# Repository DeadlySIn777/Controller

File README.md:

# Visual CNC controller — engineering workspace

Documentation reconciled **18 October 2026** against recorded decisions and evidence. The controller has working disconnected software, LinuxCNC/RTL integration and substantial native electrical/PCB work. Routing, complete electrical qualification, FPGA physical implementation and physical machine qualification remain unfinished. **There is no manufacturing release.**

## Start here

| Document | Purpose |
| --- | --- |
| [Complete documentation index](docs/README.md) | All topic guides, component documentation and historical evidence |
| [Project briefing](PROJECT_BRIEFING.md) | Product, architecture, implemented work and remaining work |
| [Project memory](PROJECT_MEMORY.md) | User decisions and constraints to preserve |
| [Engineering status](reports/ENGINEERING_STATUS.md) | Latest recorded results, exact sources and limitations |
| [Current acceptance gates](docs/CURRENT_ACCEPTANCE_GATES.md) | Requirements still needed for release |
| [Build plan](docs/BUILD_PLAN.md) and [platform roadmap](docs/PLATFORM_ROADMAP.md) | Execution order and proposed capabilities |

## Current product contract

[IS-2](docs/MOTHERBOARD_IS2.md) requires **one active custom motherboard with a soldered FPGA and all twelve motor interfaces fitted**, individual enable/alarm on all twelve, at least eight usable motors, four base ABZ encoders, 24 general DI and 16 smart general DO, plus the specified fast inputs, process/analog interfaces, communications, protection and watchdog/permission circuitry. Purchased compute, ESP and storage/settings modules remain replaceable. The older passive base, removable custom motion/I/O cards and motors-9–12 expansion card are superseded.

Local LinuxCNC owns motion planning; the FPGA supplies deterministic timing/capture and the ESP has a bounded diagnostic/service role. Accessory automation is a separately qualified extension. The touchscreen, CLI and optional AI proposals share validation and reversible configuration transactions. Normal operation and recovery remain available offline without AI credits. See [setup](docs/SETUP_WORKBENCH.md), [configuration](docs/CONFIGURATION_AND_CLI.md), [diagnostics](docs/DIAGNOSTICS_AND_PACKAGES.md) and [OS experience](docs/CONTROLLER_OS.md).

Screen options cover the **7-, 10-, 12-, 14-, 18- and 21-inch classes and further qualified sizes**. Screen size and software licensing do not remove fitted motor channels or required I/O. Every package must include and cost its stated display, compute, supplies, enclosure, harnesses and setup scope. See [display tiers](docs/DISPLAY_TIERS.md) and [commercial policy](docs/COMMERCIAL_MODEL_AND_LICENSING.md).

Power-off service exchanges an approved commodity module or the whole motherboard using keyed pluggable terminal/harness groups. Preserve protected machine settings, mirror/export recovery, offline entitlement and deliberate inhibited restart. Whole-board service has its own verification and cost requirements; no five-minute replacement guarantee is established. See [repair and machine memory](docs/MODULAR_REPAIR_AND_MEMORY.md).

## Evidence to read in context

| Scope | Recorded result | Boundary |
| --- | --- | --- |
| Adopted Source26/ROOT104, published CAD30 | 3,508 required joins remain; native ordinary DRC 0 errors/0 warnings; Source26 ERC 0 errors/70 warnings | Dated adopted source, distinct from later isolated finishing work |
| [17 October finishing continuation](reports/board-finish-20261017/README.md) | Recovered R299 full native result: 1,172 required joins / 1,183 API items, 0 ordinary errors/333 warnings/0 parity issues | Unfinished continuation; no adoption or manufacturing promotion |
| Isolated corrected baseline in that continuation | Same 1,172 joins; cached-fill DRC 0 ordinary errors/332 warnings/0 parity issues | Duplicate-via/BOM correction; no fresh refill in that check |
| Composed routing stages 1–4 | Native input/source/geometry checks recorded; full refill/AFTER qualification remains open in the cited report | Stale cached fills cannot establish new connectivity or ratings |
| Canonical disconnected SIM2 correction | Actual full-core mapping: 15,805 LUT4 + 2,107 ADD = 17,912; 63 RAM5K; fresh eight-/twelve-joint LinuxCNC/C/SPI/RTL/virtual-feedback checks | Functional mapping and simulation; physical wrapper, vendor place/route and timing remain open |
| Historical CNC1 baseline | [Six-joint/two-encoder integration](reports/CNC1_INTEGRATION.md), [synthesis](reports/FPGA_SYNTHESIS.md) and [recovery](reports/PERSISTENT_RUNTIME.md) | Preserve the original tested source, date, limits and profile |

Use the source-bound [engineering status](reports/ENGINEERING_STATUS.md) and continuation receipts before quoting a count. Source inspection, host tests, target compilation, HDL simulation, FPGA mapping, circuit ERC, board DRC and physical measurements establish different things. No physical commissioning or complete machine rating follows from the table.

The immutable [Source26 cost audit v11](reports/motherboard-cost-20260930/source-r26-2688-complete-cost-v11/README.md) is a dated partial basket: 105 exact MPNs priced, 185 MPNs/720 fitted pieces unpriced. Known-priced consumed parts at 1/10/100 controllers are US$1,091.51/$877.37/$796.51 per board. Modules, displays, fabrication, assembly, programming/test and packaging remain additional unknowns. US$400 is a preliminary assembly reference; a complete product cost or PCBWay quote is not established.

## Use the disconnected workbench

From this directory, with the required Python dependencies available:

```powershell
python -B -m controller_config setup --directory .controller-setup-demo serve --port 8766
```

Open `http://127.0.0.1:8766/`. This starts the local simulation setup UI and shared service. It does not commission or authorize a physical machine. The [workbench guide](docs/SETUP_WORKBENCH.md) describes intake, readiness, reviewed saves, backup recovery and optional AI budgets. Use a separate demonstration directory to preserve existing machine configurations.

To inspect the engineering bench before choosing checks:

```powershell
python -X utf8 tools/validate_controller.py --inventory
```

The documented full disconnected bench is `./validate_controller.ps1 --full` or `python -X utf8 tools/validate_controller.py --full`. It creates a new evidence directory. Missing tools and unfinished stages remain explicitly blocked; physical tests remain unrun. See [Rev A qualification](docs/REV_A_QUALIFICATION.md) and the [PCBWay submission checklist](manufacturing/PCBWAY_SUBMISSION_CHECKLIST.md).

The [200-feature catalogue](docs/FEATURE_CATALOG.md) preserves proposals and stable IDs. Dated research, component READMEs and report snapshots keep their original evidence scope; use the [documentation index](docs/README.md) to find current guidance before interpreting them as product capabilities.

## Published native board snapshot

The existing [board-review package](BOARD_REVIEW.md), its native baseline/staged files and original provenance remain available alongside the complete engineering source. See [GitHub publication scope](GITHUB_PUBLICATION.md) for the source/evidence inventory.

The [corrected global reroute start](board/global-reroute-start/board.kicad_pro), [clean DSN](routing/TMR-clean-plane-free-F-In3-B-domain600-r6.dsn) and [converter setup correction](review/TMR-setup-correction.md) are also available. They restore five malformed keepouts and remove 359 conflicting copper items for rerouting; native AFTER connectivity and manufacturing qualification remain open.

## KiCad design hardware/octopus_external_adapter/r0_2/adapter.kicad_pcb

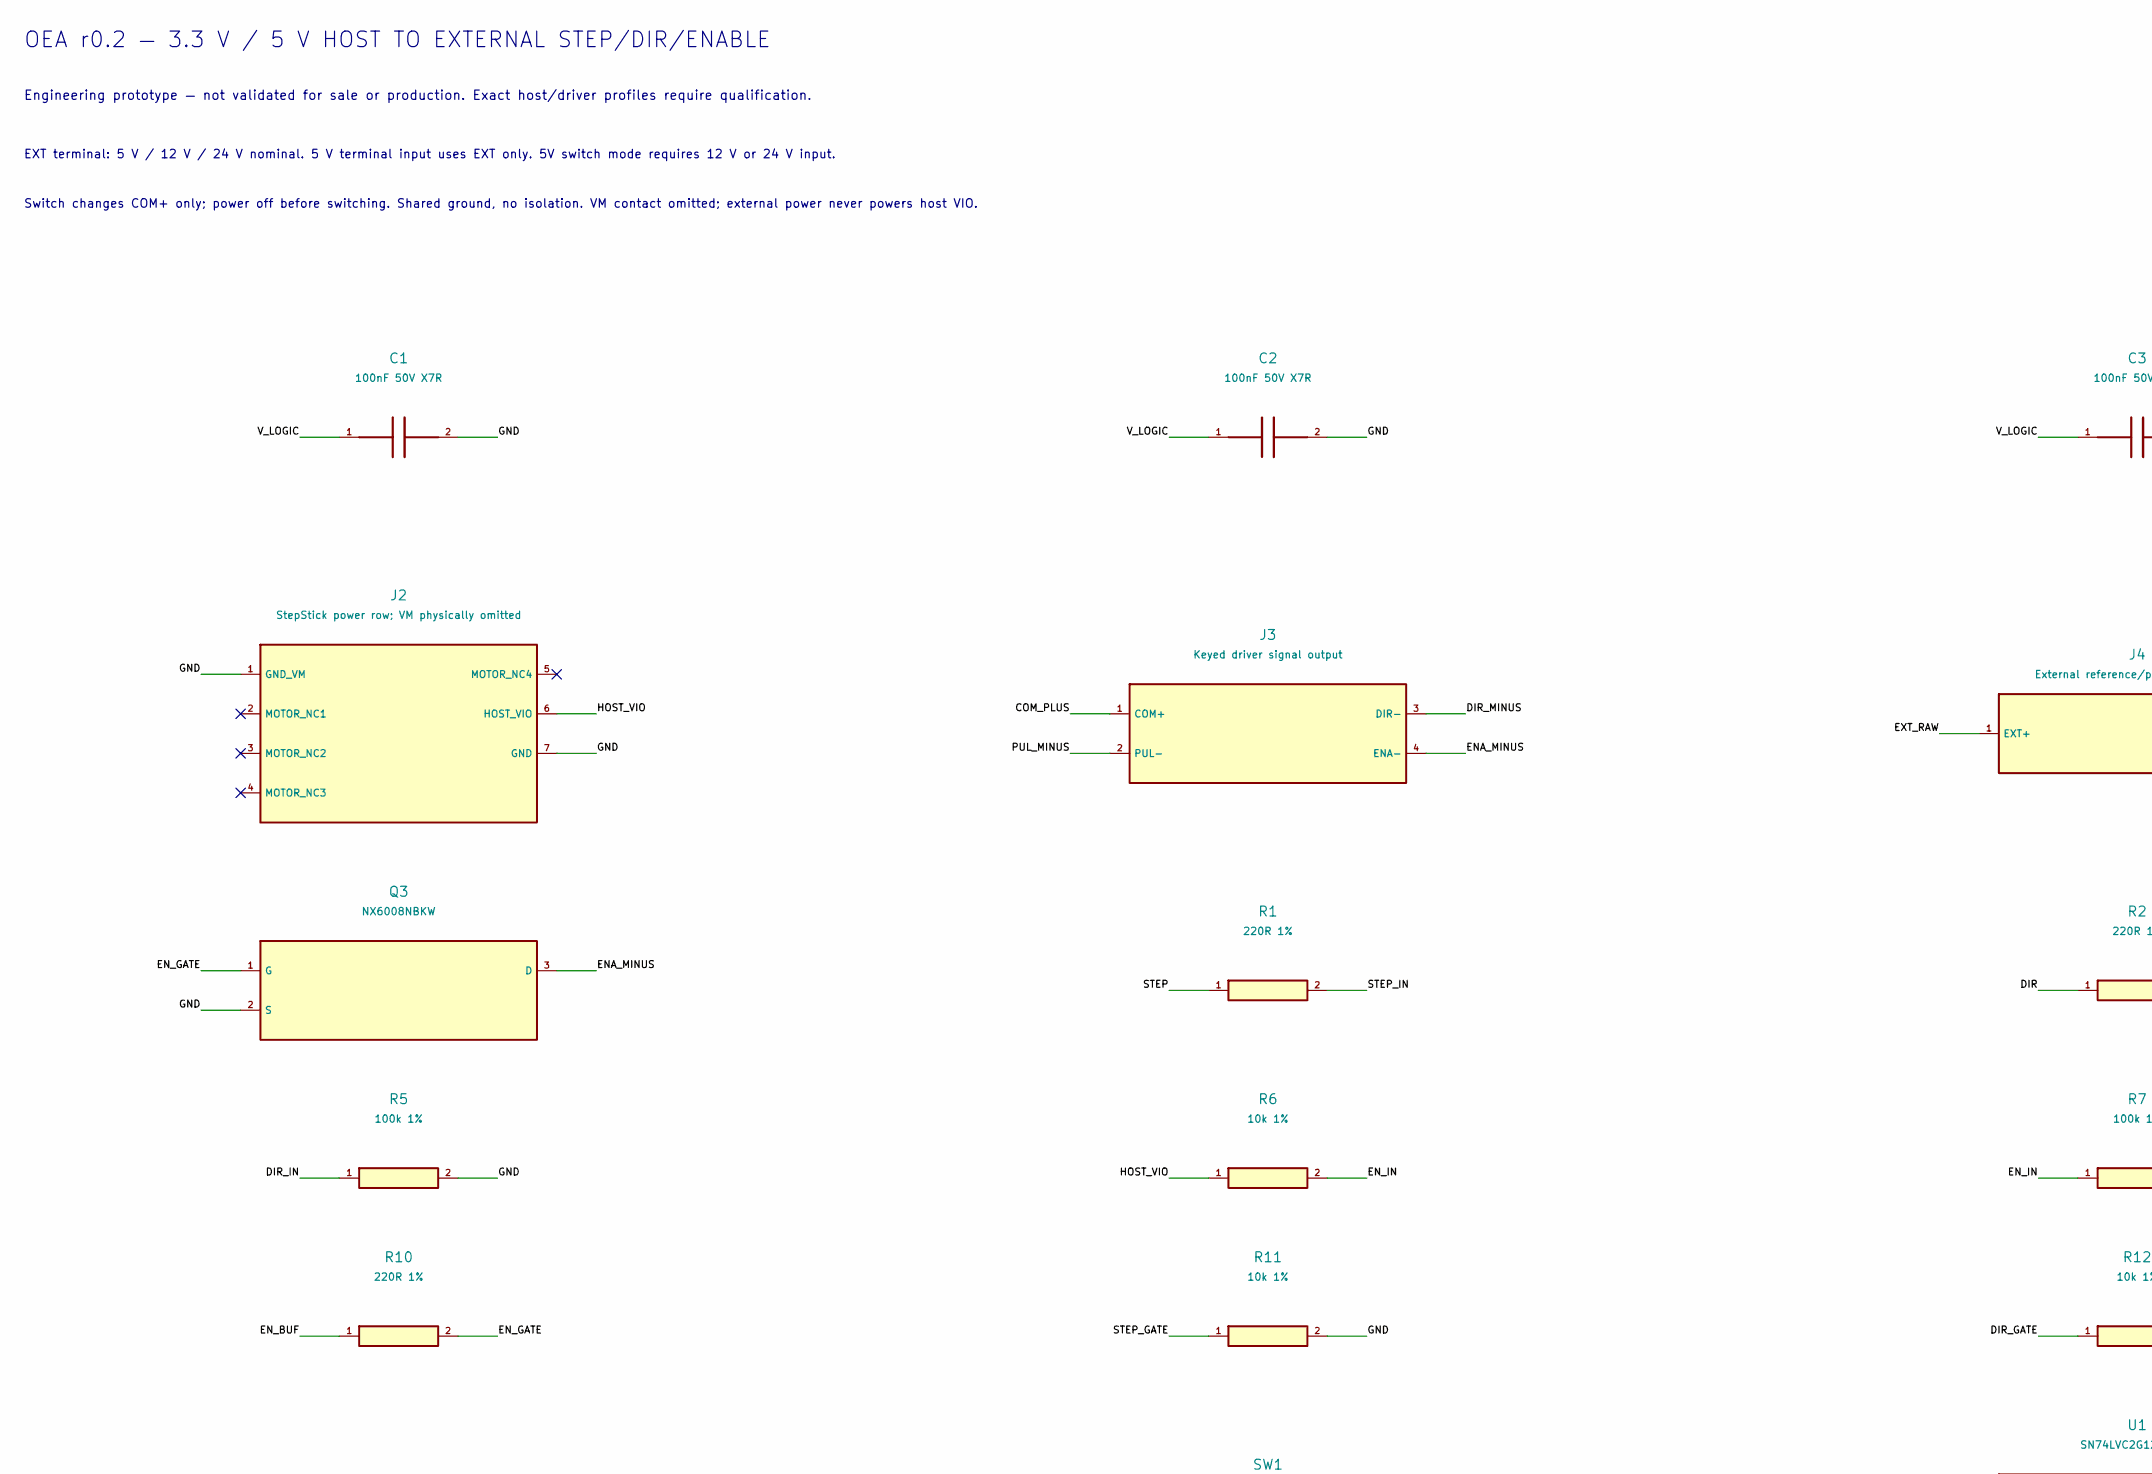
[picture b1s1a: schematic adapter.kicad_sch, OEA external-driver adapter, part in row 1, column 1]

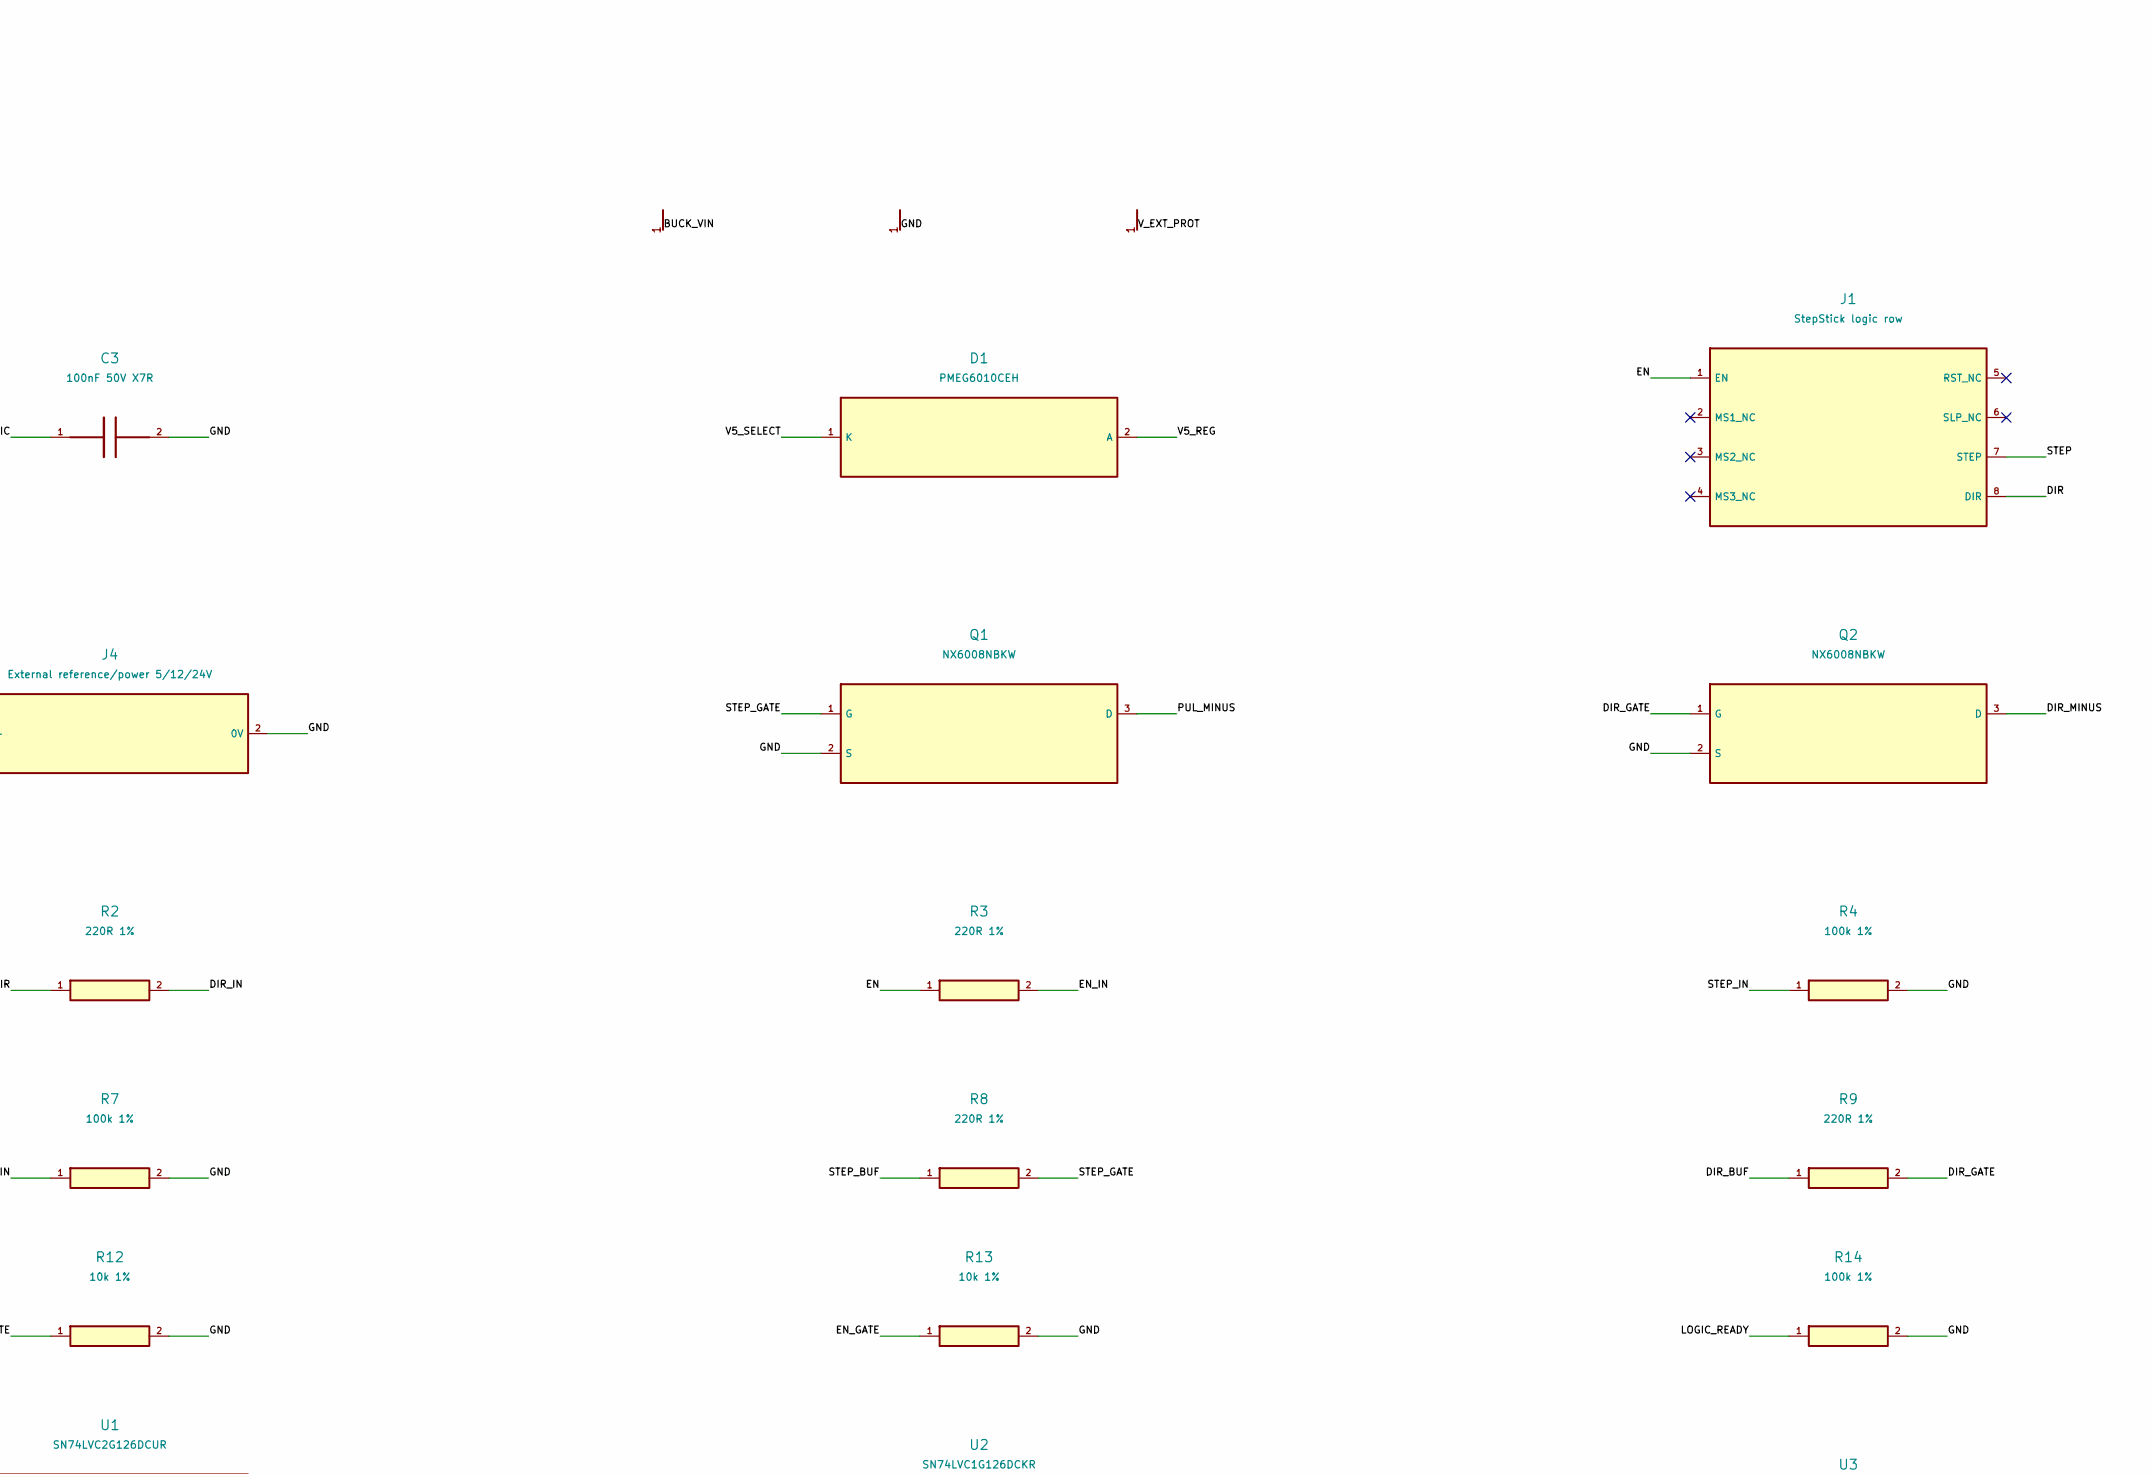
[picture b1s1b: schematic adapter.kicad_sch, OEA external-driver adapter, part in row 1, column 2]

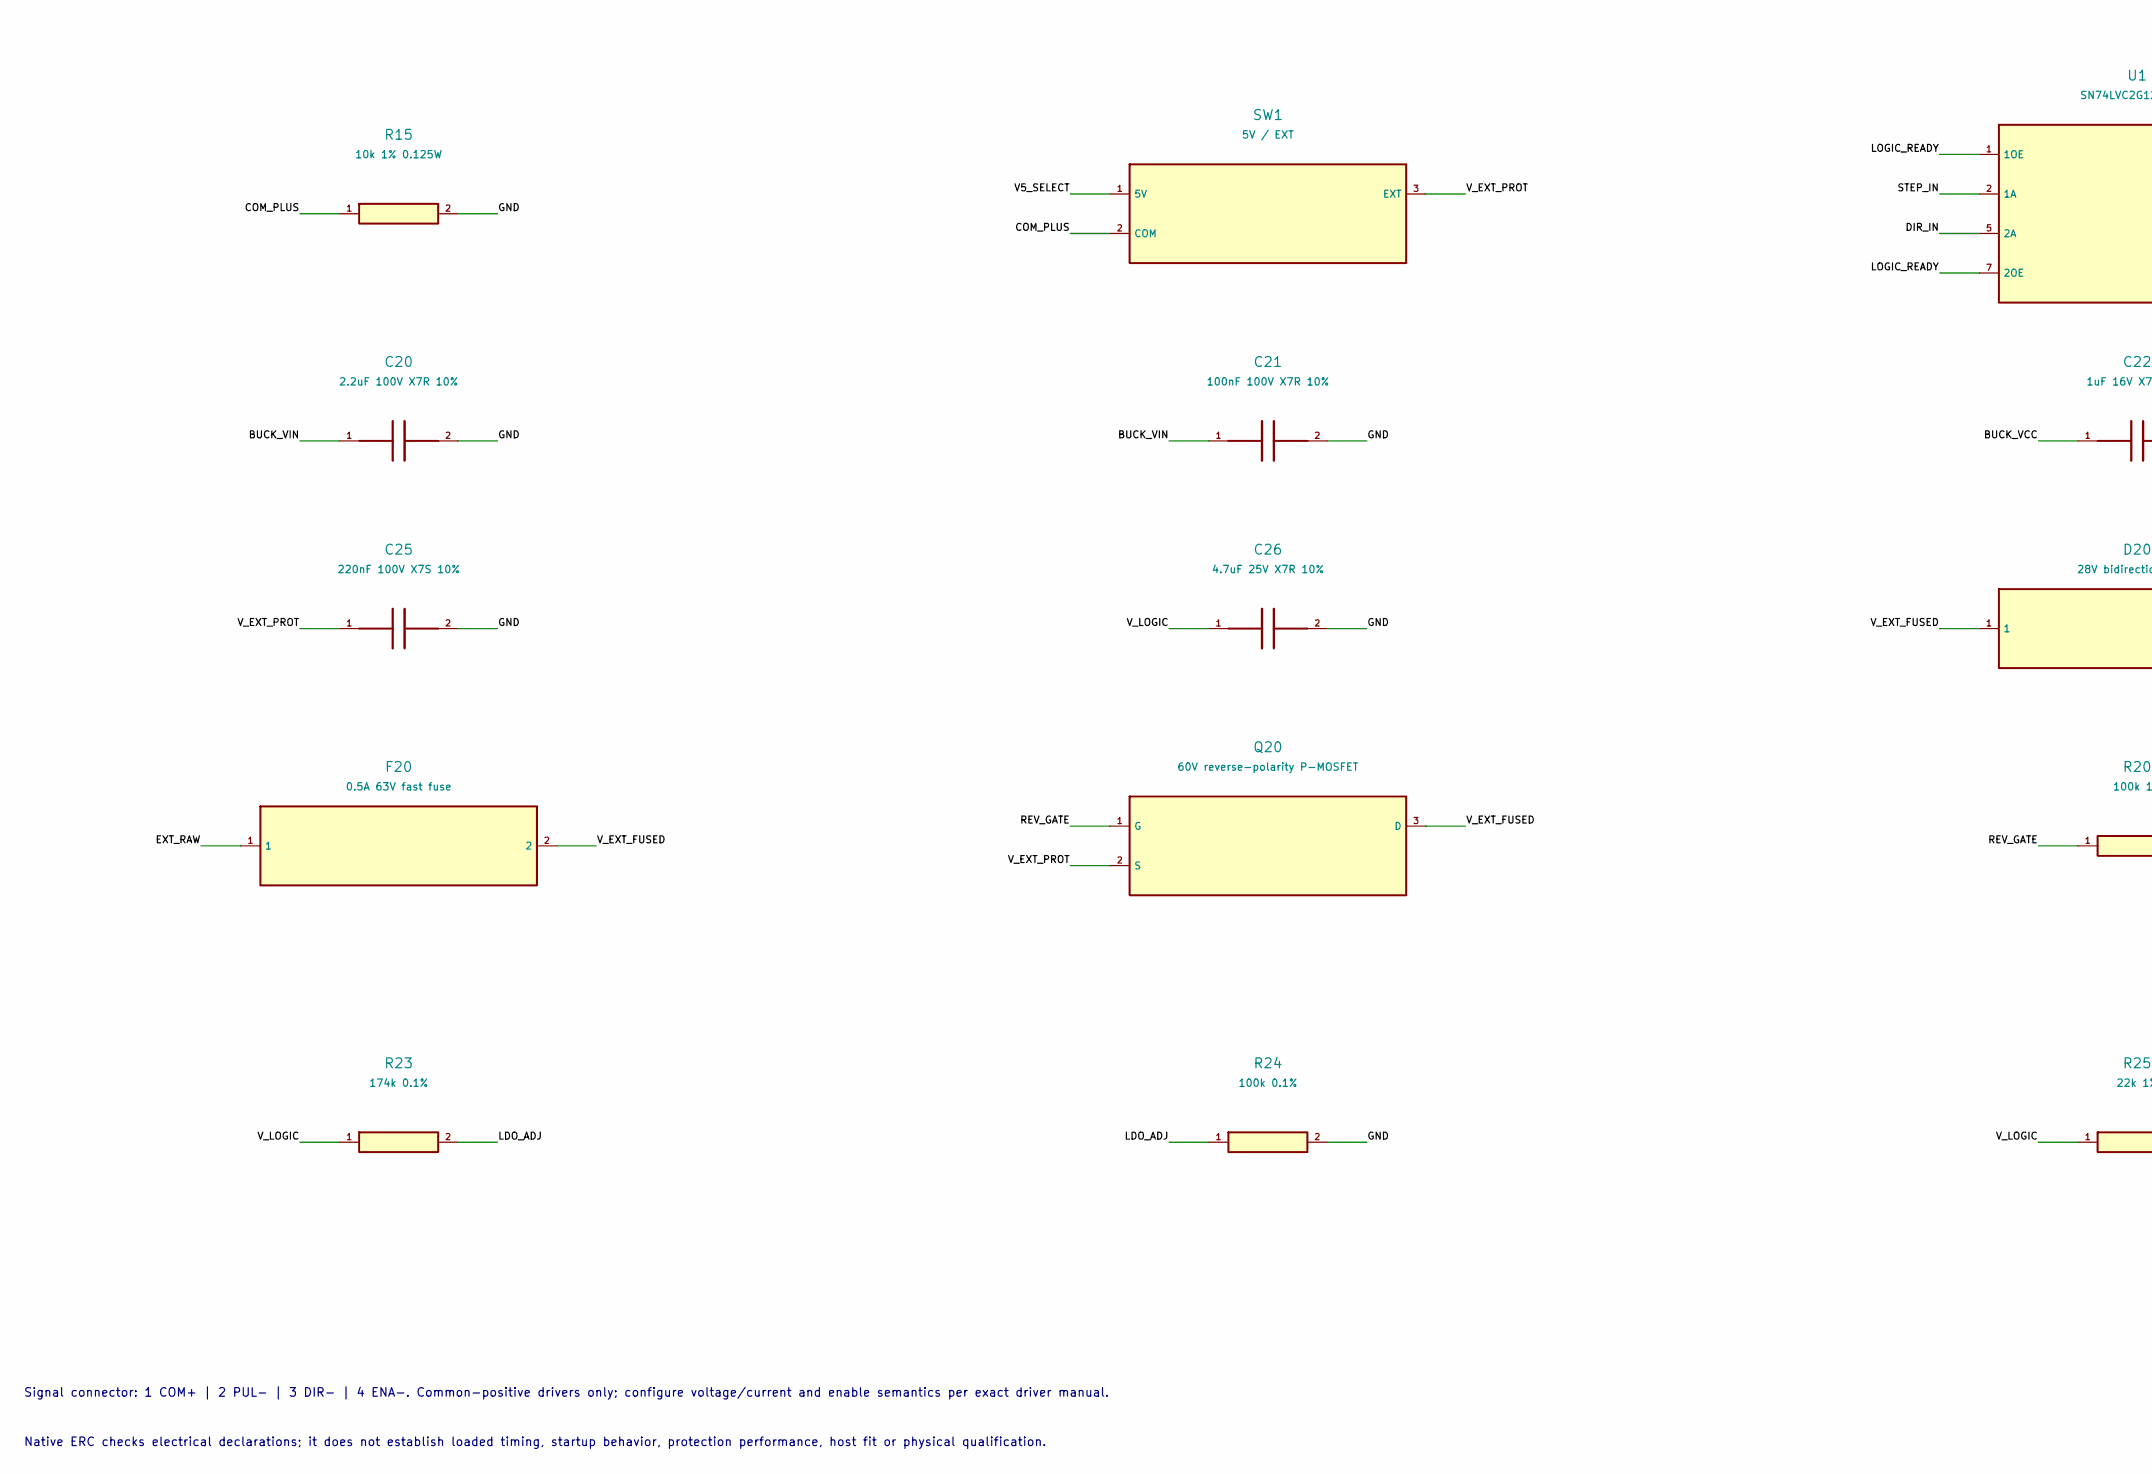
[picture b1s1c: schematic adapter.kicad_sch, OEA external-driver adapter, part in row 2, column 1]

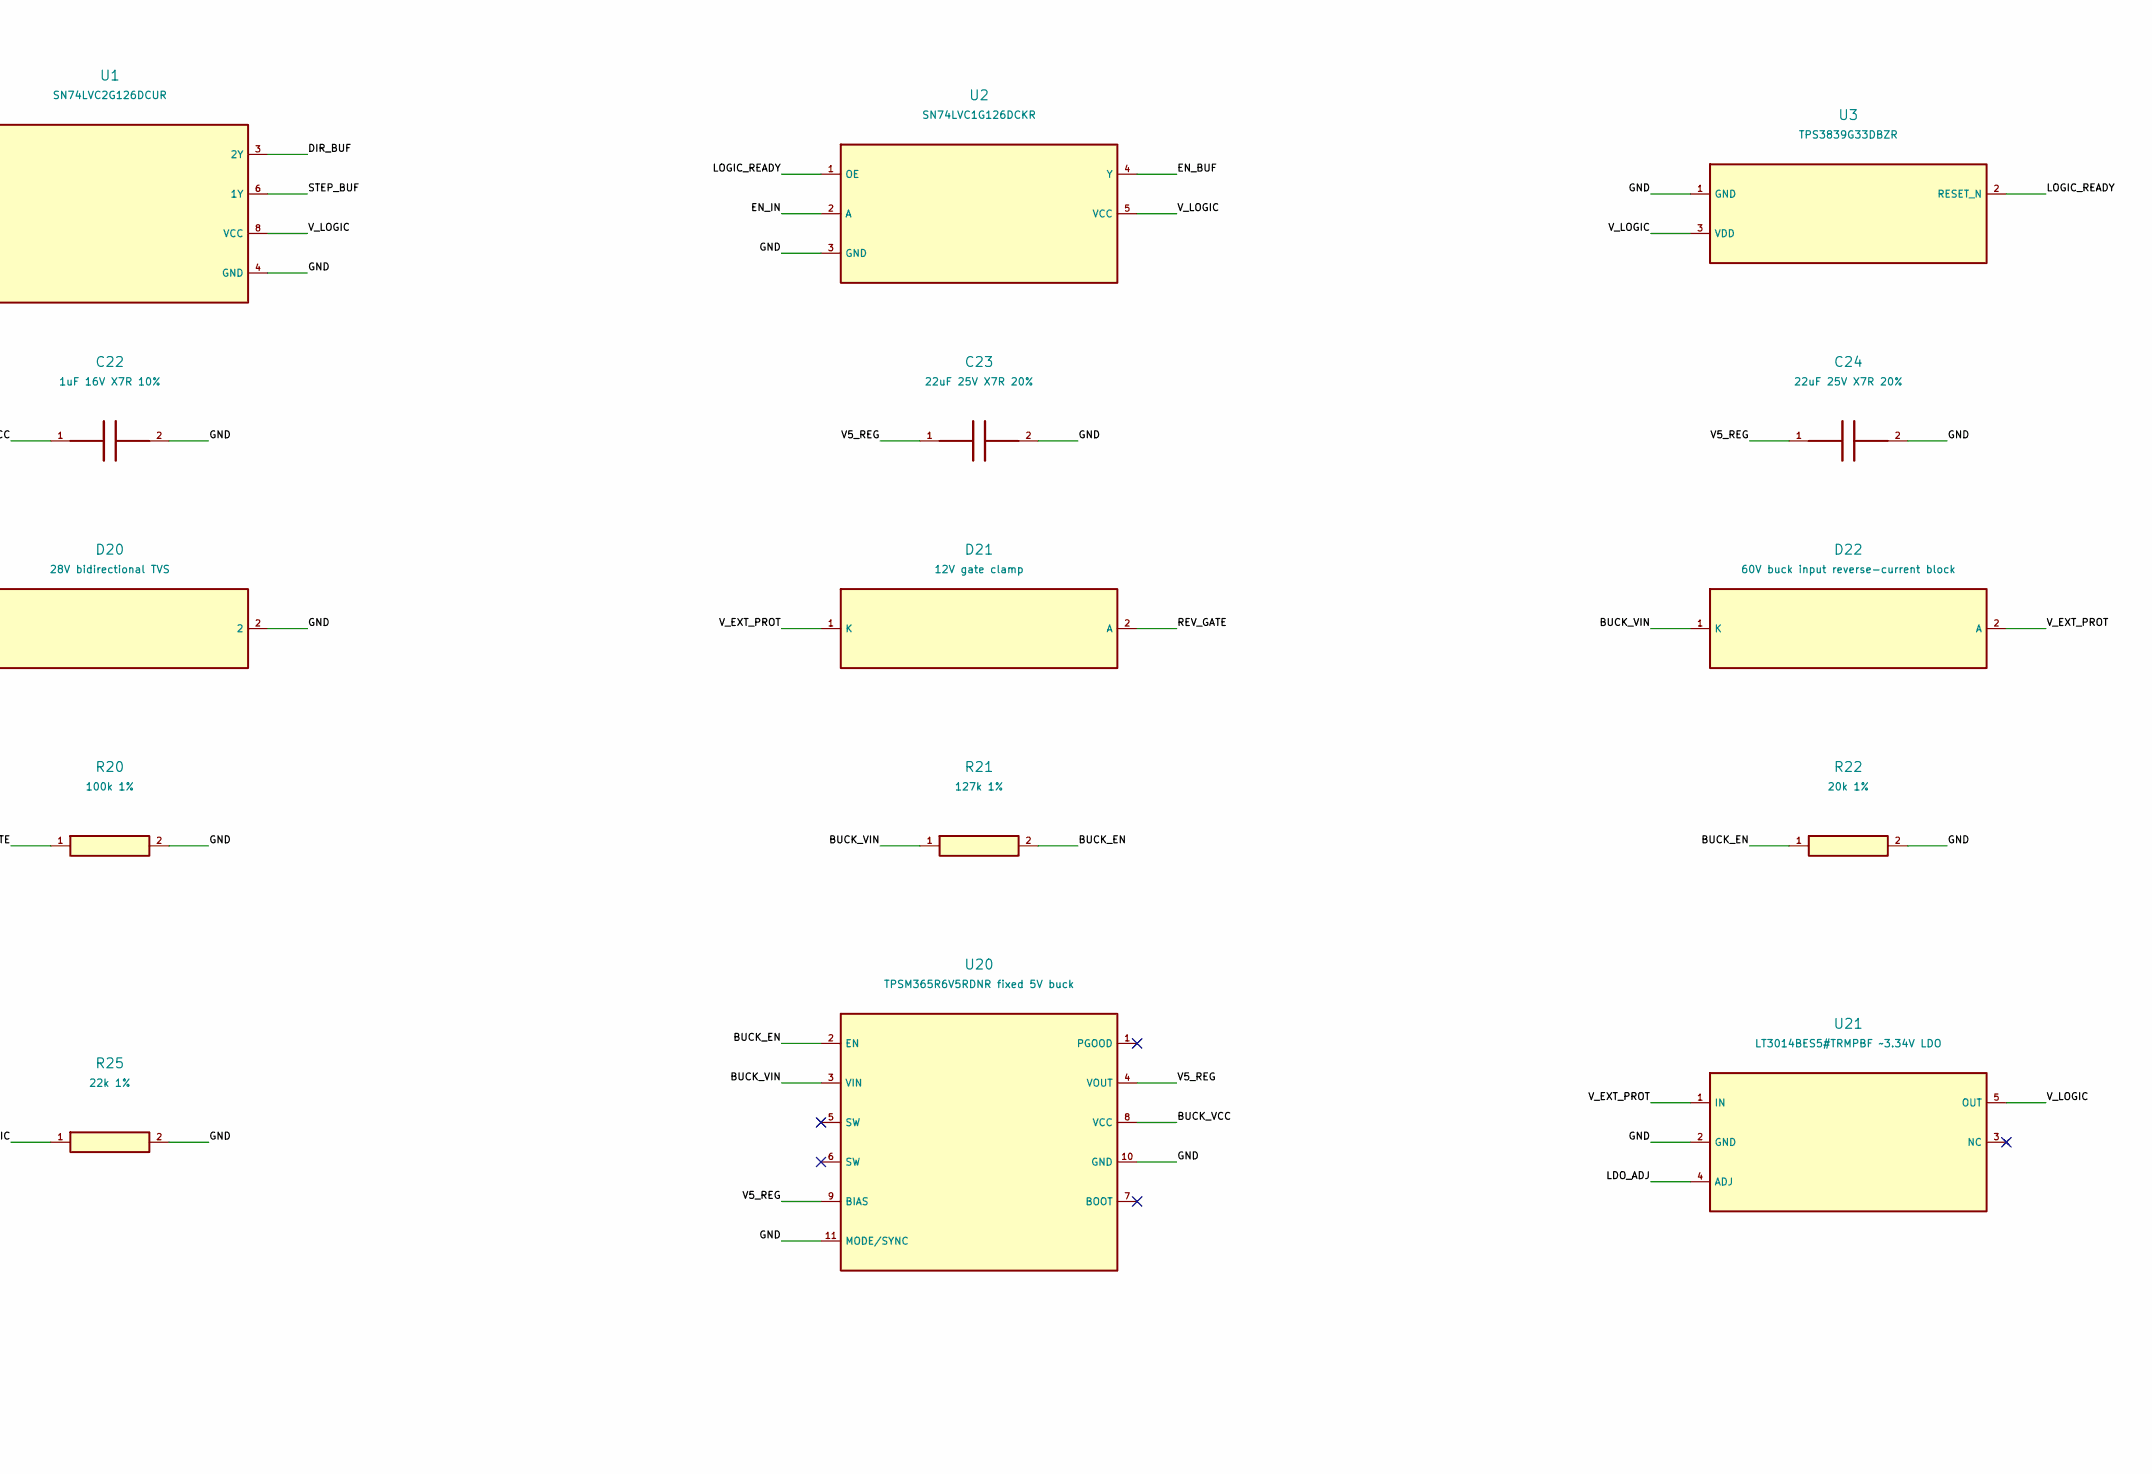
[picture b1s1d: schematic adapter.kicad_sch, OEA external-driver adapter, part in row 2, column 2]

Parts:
C1, C2, C3: 100nF 50V X7R; C_0603_1608Metric; MPN CL10B104KB8NNNC
C20: 2.2uF 100V X7R 10%; C_1210_3225Metric; MPN C3225X7R2A225K230AB
C21: 100nF 100V X7R 10%; C_0603_1608Metric; MPN GRM188R72A104KA35J
C22: 1uF 16V X7R 10%; C_0603_1608Metric; MPN C1608X7R1C105K080AC
C23, C24: 22uF 25V X7R 20%; C_1210_3225Metric; MPN C3225X7R1E226M250AB
C25: 220nF 100V X7S 10%; C_0805_2012Metric; MPN C2012X7S2A224K085AE
C26: 4.7uF 25V X7R 10%; C_0805_2012Metric; MPN CL21B475KAFNNNE
D1: PMEG6010CEH; D_SOD-123F; MPN PMEG6010CEH,115
D20: 28V bidirectional TVS; D_SMA; MPN SMAJ28CA-13-F
D21: 12V gate clamp; D_SOD-123; MPN BZT52C12-7-F
D22: 60V buck input reverse-current block; D_SOD-123F; MPN PMEG6010CEH,115
F20: 0.5A 63V fast fuse; Bourns_SF-1206F_3.1x1.55mm; MPN SF-1206F050-2
J1: StepStick logic row; Wurth_61300811121_1x08_P2.54mm; MPN 61300811121
J2: StepStick power row; VM physically omitted; Wurth_61300711121_1x07_P2.54mm; MPN 61300711121
J3: Keyed driver signal output; JST_XH_B4B-XH-A_1x04_P2.50mm_Vertical; MPN B4B-XH-A(LF)(SN)
J4: External reference/power 5/12/24V; Phoenix_1725656_MPT_0p5_2_2p54_SilkClearance; MPN 1725656
Q1, Q2, Q3: NX6008NBKW; SOT-323_SC-70; MPN NX6008NBKW,115
Q20: 60V reverse-polarity P-MOSFET; SOT-23; MPN PMV100EPAR
R1, R2, R3, R8, R9, R10: 220R 1%; R_0603_1608Metric; MPN RC0603FR-07220RL
R4, R5, R7, R14, R20: 100k 1%; R_0603_1608Metric; MPN RC0603FR-07100KL
R6, R11, R12, R13: 10k 1%; R_0603_1608Metric; MPN RC0603FR-0710KL
R15: 10k 1% 0.125W; R_0805_2012Metric; MPN RC0805FR-0710KL
R21: 127k 1%; R_0603_1608Metric; MPN RC0603FR-07127KL
R22: 20k 1%; R_0603_1608Metric; MPN RC0603FR-0720KL
R23: 174k 0.1%; R_0603_1608Metric; MPN RT0603BRD07174KL
R24: 100k 0.1%; R_0603_1608Metric; MPN RT0603BRD07100KL
R25: 22k 1%; R_0603_1608Metric; MPN RC0603FR-0722KL
SW1: 5V / EXT; E-Switch_EG1218_P040040; MPN EG1218
U1: SN74LVC2G126DCUR; VSSOP-8_2.3x2mm_P0.5mm; MPN SN74LVC2G126DCUR
U2: SN74LVC1G126DCKR; SOT-353_SC-70-5; MPN SN74LVC1G126DCKR
U3: TPS3839G33DBZR; SOT-23; MPN TPS3839G33DBZR
U20: TPSM365R6V5RDNR fixed 5V buck; TI_RDN0011A_TPSM365R6; MPN TPSM365R6V5RDNR
U21: LT3014BES5#TRMPBF ~3.34V LDO; TSOT-23-5; MPN LT3014BES5#TRMPBF

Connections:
/BUCK_EN: R21.2, R22.1, U20.2 (EN)
/BUCK_VCC: C22.1, U20.8 (VCC)
/BUCK_VIN: C20.1, C21.1, D22.1 (K), R21.1, U20.3 (VIN)
/COM_PLUS: J3.1 (COM+), R15.1, SW1.2 (COM)
/DIR: J1.8 (DIR), R2.1
/DIR_BUF: R9.1, U1.3 (2Y)
/DIR_GATE: Q2.1 (G), R9.2, R12.1
/DIR_IN: R2.2, R5.1, U1.5 (2A)
/DIR_MINUS: J3.3 (DIR-), Q2.3 (D)
/EN: J1.1 (EN), R3.1
/ENA_MINUS: J3.4 (ENA-), Q3.3 (D)
/EN_BUF: R10.1, U2.4 (Y)
/EN_GATE: Q3.1 (G), R10.2, R13.1
/EN_IN: R3.2, R6.2, R7.1, U2.2 (A)
/EXT_RAW: F20.1, J4.1 (EXT+)
/GND: C1.2, C2.2, C3.2, C20.2, C21.2, C22.2, C23.2, C24.2, C25.2, C26.2, D20.2, J2.1 (GND_VM), J2.7 (GND), J4.2 (0V), Q1.2 (S), Q2.2 (S), Q3.2 (S), R4.2, R5.2, R7.2, R11.2, R12.2, R13.2, R14.2, R15.2, R20.2, R22.2, R24.2, R25.2, U1.4 (GND), U2.3 (GND), U3.1 (GND), U20.10 (GND), U20.11 (MODE/SYNC), U21.2 (GND)
/HOST_VIO: J2.6 (HOST_VIO), R6.1
/LDO_ADJ: R23.2, R24.1, U21.4 (ADJ)
/LOGIC_READY: R14.1, U1.1 (1OE), U1.7 (2OE), U2.1 (OE), U3.2 (RESET_N)
/PUL_MINUS: J3.2 (PUL-), Q1.3 (D)
/REV_GATE: D21.2 (A), Q20.1 (G), R20.1
/STEP: J1.7 (STEP), R1.1
/STEP_BUF: R8.1, U1.6 (1Y)
/STEP_GATE: Q1.1 (G), R8.2, R11.1
/STEP_IN: R1.2, R4.1, U1.2 (1A)
/V5_REG: C23.1, C24.1, D1.2 (A), U20.4 (VOUT), U20.9 (BIAS)
/V5_SELECT: D1.1 (K), SW1.1 (5V)
/V_EXT_FUSED: D20.1, F20.2, Q20.3 (D)
/V_EXT_PROT: C25.1, D21.1 (K), D22.2 (A), Q20.2 (S), SW1.3 (EXT), U21.1 (IN)
/V_LOGIC: C1.1, C2.1, C3.1, C26.1, R23.1, R25.1, U1.8 (VCC), U2.5 (VCC), U3.3 (VDD), U21.5 (OUT)

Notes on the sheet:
OEA r0.2 — 3.3 V / 5 V HOST TO EXTERNAL STEP/DIR/ENABLE
Engineering prototype — not validated for sale or production. Exact host/driver profiles require qualification.
EXT terminal: 5 V / 12 V / 24 V nominal. 5 V terminal input uses EXT only. 5V switch mode requires 12 V or 24 V input.
Switch changes COM+ only; power off before switching. Shared ground, no isolation. VM contact omitted; external power never powers host VIO.
Signal connector: 1 COM+ | 2 PUL− | 3 DIR− | 4 ENA−. Common-positive drivers only; configure voltage/current and enable semantics per exact driver manual.
Native ERC checks electrical declarations; it does not establish loaded timing, startup behavior, protection performance, host fit or physical qualification.

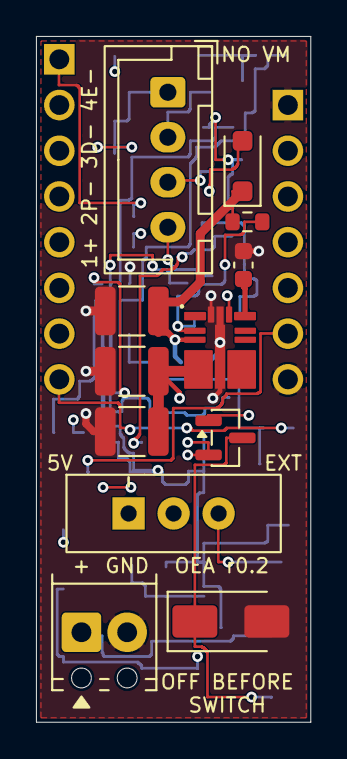
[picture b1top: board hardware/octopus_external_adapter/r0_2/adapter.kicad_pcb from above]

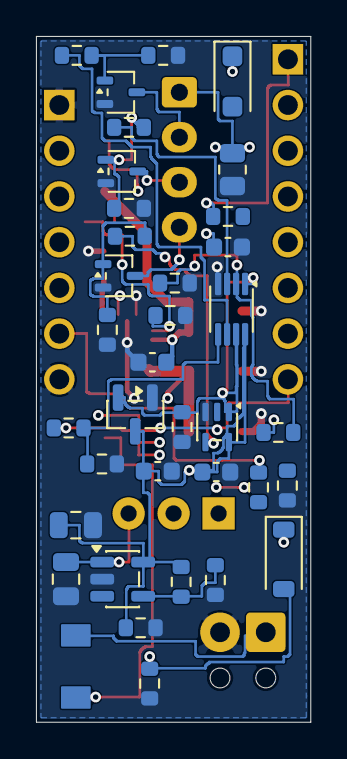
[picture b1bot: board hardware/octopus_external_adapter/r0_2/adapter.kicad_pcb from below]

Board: 4 copper layers, 15.2 x 38.1 mm, 50 parts (38 on the bottom side), 30 nets.

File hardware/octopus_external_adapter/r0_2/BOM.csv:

Item,Designators,Quantity per board,Quantity for 5 boards,Manufacturer,Manufacturer part number,Description / value,Footprint,Mounting,Assembly side by reference,Fit,Assembly notes
1,"C1, C2, C3",3,15,Samsung Electro-Mechanics,CL10B104KB8NNNC,100nF 50V X7R,Capacitor_SMD:C_0603_1608Metric,SMT,C1: Bottom; C2: Bottom; C3: Bottom,Yes,No substitutions without engineering approval.
2,C20,1,5,TDK,C3225X7R2A225K230AB,2.2uF 100V X7R 10%,Capacitor_SMD:C_1210_3225Metric,SMT,C20: Top,Yes,No substitutions without engineering approval.
3,C21,1,5,Murata,GRM188R72A104KA35J,100nF 100V X7R 10%,Capacitor_SMD:C_0603_1608Metric,SMT,C21: Bottom,Yes,No substitutions without engineering approval.
4,C22,1,5,TDK,C1608X7R1C105K080AC,1uF 16V X7R 10%,Capacitor_SMD:C_0603_1608Metric,SMT,C22: Top,Yes,No substitutions without engineering approval.
5,"C23, C24",2,10,TDK,C3225X7R1E226M250AB,22uF 25V X7R 20%,Capacitor_SMD:C_1210_3225Metric,SMT,C23: Top; C24: Top,Yes,No substitutions without engineering approval.
6,C25,1,5,TDK,C2012X7S2A224K085AE,220nF 100V X7S 10%,Capacitor_SMD:C_0805_2012Metric,SMT,C25: Bottom,Yes,No substitutions without engineering approval.
7,C26,1,5,Samsung Electro-Mechanics,CL21B475KAFNNNE,4.7uF 25V X7R 10%,Capacitor_SMD:C_0805_2012Metric,SMT,C26: Bottom,Yes,No substitutions without engineering approval.
8,"D1, D22",2,10,Nexperia,"PMEG6010CEH,115",PMEG6010CEH; 60V buck input reverse-current block,Diode_SMD:D_SOD-123F,SMT,D1: Bottom; D22: Top,Yes,No substitutions without engineering approval.
9,D20,1,5,Diodes Incorporated,SMAJ28CA-13-F,28V bidirectional TVS,Diode_SMD:D_SMA,SMT,D20: Top,Yes,No substitutions without engineering approval.
10,D21,1,5,Diodes Incorporated,BZT52C12-7-F,12V gate clamp,Diode_SMD:D_SOD-123,SMT,D21: Bottom,Yes,No substitutions without engineering approval.
11,F20,1,5,Bourns,SF-1206F050-2,0.5A 63V fast fuse,Adapter:Bourns_SF-1206F_3.1x1.55mm,SMT,F20: Bottom,Yes,No substitutions without engineering approval.
12,J1,1,5,Wurth Elektronik,61300811121,StepStick logic row,Adapter:Wurth_61300811121_1x08_P2.54mm,THT,J1: Bottom,Yes,No substitutions without engineering approval. Long male mating posts face down into host; do not trim mating posts.
13,J2,1,5,Wurth Elektronik,61300711121,StepStick power row; VM physically omitted,Adapter:Wurth_61300711121_1x07_P2.54mm,THT,J2: Bottom,Yes,No substitutions without engineering approval. Long male mating posts face down into host; do not trim mating posts.
14,J3,1,5,JST,B4B-XH-A(LF)(SN),Keyed driver signal output,Connector_JST:JST_XH_B4B-XH-A_1x04_P2.50mm_Vertical,THT,J3: Top,Yes,No substitutions without engineering approval. Controlled underside tail trimming per assembly drawing.
15,J4,1,5,Phoenix Contact,1725656,External reference/power 5/12/24V,"TerminalBlock_Phoenix:TerminalBlock_Phoenix_MPT-0,5-2-2.54_1x02_P2.54mm_Horizontal",THT,J4: Top,Yes,No substitutions without engineering approval. Controlled underside tail trimming per assembly drawing.
16,"Q1, Q2, Q3",3,15,Nexperia,"NX6008NBKW,115",NX6008NBKW,Package_TO_SOT_SMD:SOT-323_SC-70,SMT,Q1: Bottom; Q2: Bottom; Q3: Bottom,Yes,No substitutions without engineering approval.
17,Q20,1,5,Nexperia,PMV100EPAR,60V reverse-polarity P-MOSFET,Package_TO_SOT_SMD:SOT-23,SMT,Q20: Top,Yes,No substitutions without engineering approval.
18,"R1, R2, R3, R8, R9, R10",6,30,Yageo,RC0603FR-07220RL,220R 1%,Resistor_SMD:R_0603_1608Metric,SMT,R1: Bottom; R2: Bottom; R3: Bottom; R8: Bottom; R9: Bottom; R10: Bottom,Yes,No substitutions without engineering approval.
19,"R4, R5, R7, R14, R20",5,25,Yageo,RC0603FR-07100KL,100k 1%,Resistor_SMD:R_0603_1608Metric,SMT,R4: Bottom; R5: Bottom; R7: Bottom; R14: Bottom; R20: Bottom,Yes,No substitutions without engineering approval.
20,"R6, R11, R12, R13",4,20,Yageo,RC0603FR-0710KL,10k 1%,Resistor_SMD:R_0603_1608Metric,SMT,R6: Bottom; R11: Bottom; R12: Bottom; R13: Bottom,Yes,No substitutions without engineering approval.
21,R15,1,5,Yageo,RC0805FR-0710KL,10k 1% 0.125W,Resistor_SMD:R_0805_2012Metric,SMT,R15: Bottom,Yes,No substitutions without engineering approval.
22,R21,1,5,Yageo,RC0603FR-07127KL,127k 1%,Resistor_SMD:R_0603_1608Metric,SMT,R21: Bottom,Yes,No substitutions without engineering approval.
23,R22,1,5,Yageo,RC0603FR-0720KL,20k 1%,Resistor_SMD:R_0603_1608Metric,SMT,R22: Bottom,Yes,No substitutions without engineering approval.
24,R23,1,5,Yageo,RT0603BRD07174KL,174k 0.1%,Resistor_SMD:R_0603_1608Metric,SMT,R23: Bottom,Yes,No substitutions without engineering approval.
25,R24,1,5,Yageo,RT0603BRD07100KL,100k 0.1%,Resistor_SMD:R_0603_1608Metric,SMT,R24: Bottom,Yes,No substitutions without engineering approval.
26,R25,1,5,Yageo,RC0603FR-0722KL,22k 1%,Resistor_SMD:R_0603_1608Metric,SMT,R25: Bottom,Yes,No substitutions without engineering approval.
27,SW1,1,5,E-Switch,EG1218,5V / EXT,Adapter:E-Switch_EG1218_P040040,THT,SW1: Top,Yes,No substitutions without engineering approval. Controlled underside tail trimming per assembly drawing.
28,U1,1,5,Texas Instruments,SN74LVC2G126DCUR,SN74LVC2G126DCUR,Package_SO:VSSOP-8_2.3x2mm_P0.5mm,SMT,U1: Bottom,Yes,No substitutions without engineering approval.
29,U2,1,5,Texas Instruments,SN74LVC1G126DCKR,SN74LVC1G126DCKR,Package_TO_SOT_SMD:SOT-353_SC-70-5,SMT,U2: Bottom,Yes,No substitutions without engineering approval.
30,U3,1,5,Texas Instruments,TPS3839G33DBZR,TPS3839G33DBZR,Package_TO_SOT_SMD:SOT-23,SMT,U3: Bottom,Yes,No substitutions without engineering approval.
31,U20,1,5,Texas Instruments,TPSM365R6V5RDNR,TPSM365R6V5RDNR fixed 5V buck,Adapter:TI_RDN0011A_TPSM365R6,SMT,U20: Top,Yes,No substitutions without engineering approval.
32,U21,1,5,Analog Devices,LT3014BES5#TRMPBF,LT3014BES5#TRMPBF ~3.34V LDO,Package_TO_SOT_SMD:TSOT-23-5,SMT,U21: Bottom,Yes,No substitutions without engineering approval.
